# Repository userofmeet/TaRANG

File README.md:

# TaRANG

This repository contains the work I do at EMSys Lab, IIT Bombay, as a Research Assistant during my master's, under the guidance of Prof. Maryam Shojaei Baghini.

It serves as a place to keep the datasheets, research papers, code, and other technical resources related to my work.

## Contents

- Datasheets and technical documentation
- Research papers and references
- Code and implementations
- Experiments and analysis
- Notes and other useful resources

The repository will be updated as I continue working on different tasks and projects in the lab.

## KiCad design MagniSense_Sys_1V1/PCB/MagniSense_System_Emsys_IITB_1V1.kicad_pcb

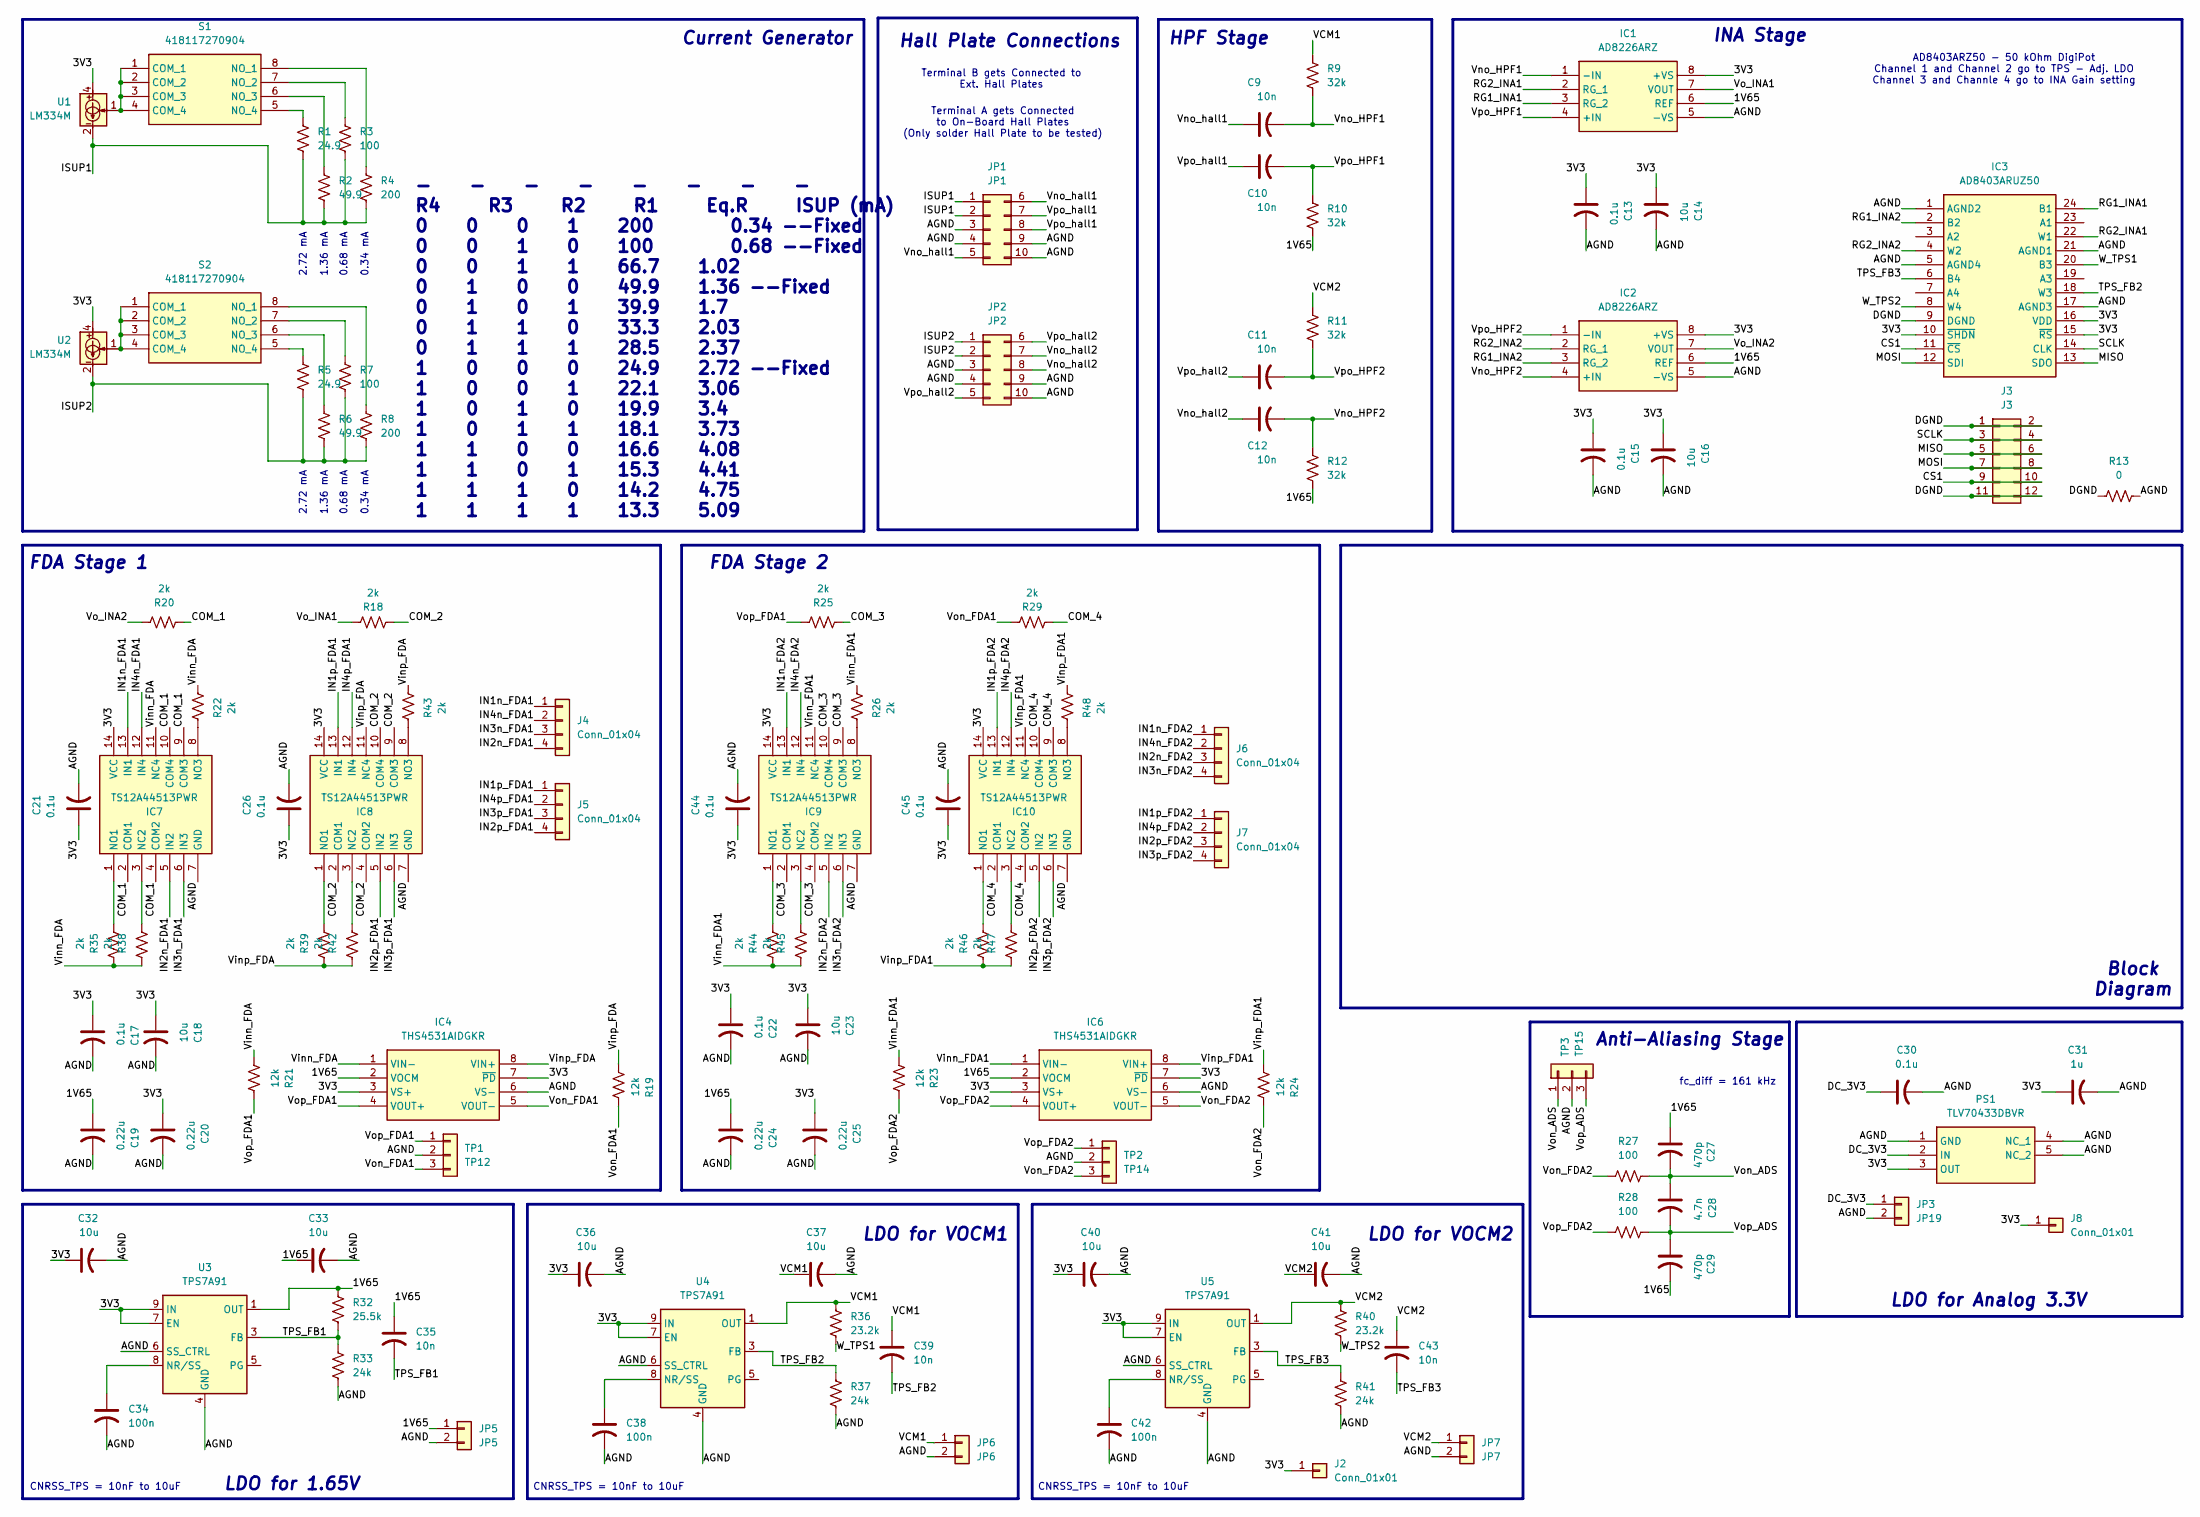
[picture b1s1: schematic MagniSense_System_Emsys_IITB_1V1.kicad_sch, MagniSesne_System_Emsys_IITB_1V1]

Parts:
C9, C10, C11, C12, C35, C39, C43: 10n; C_0603_1608Metric
C13, C15, C17, C21, C22, C26, C30, C44, C45: 0.1u; C_0603_1608Metric
C14, C16, C18, C23, C32, C33, C36, C37, C40, C41: 10u; C_0603_1608Metric
C19, C20, C24, C25: 0.22u; C_0603_1608Metric
C27, C29: 470p; C_0603_1608Metric
C28: 4.7n; C_0603_1608Metric
C31: 1u; C_0603_1608Metric
C34, C38, C42: 100n; C_0603_1608Metric
IC1, IC2: AD8226ARZ; SOIC127P600X175-8N; Manufacturer_Part_Number AD8226ARZ; Mouser Part Number 584-AD8226ARZ
IC3: AD8403ARUZ50; SOP65P640X120-24N; Manufacturer_Part_Number AD8403ARUZ50; Mouser Part Number 584-AD8403ARUZ50
IC4, IC6: THS4531AIDGKR; SOP65P490X110-8N; Manufacturer_Part_Number THS4531AIDGKR; Mouser Part Number 595-THS4531AIDGKR
IC7, IC8, IC9, IC10: TS12A44513PWR; SOP65P640X120-14N; Manufacturer_Part_Number TS12A44513PWR; Mouser Part Number 595-TS12A44513PWR
J2, J8: Conn_01x01; PinHeader_1x01_P2.54mm_Vertical
J3: J3; PinHeader_2x06_P2.54mm_Vertical
J4, J5, J6, J7: Conn_01x04; PinHeader_1x04_P2.54mm_Vertical
JP1: JP1; PinHeader_2x05_P2.54mm_Vertical
JP2: JP2; PinHeader_2x05_P2.54mm_Vertical
JP3: JP19; PinHeader_1x02_P2.54mm_Vertical
JP5: JP5; PinHeader_1x02_P2.54mm_Vertical
JP6: JP6; PinHeader_1x02_P2.54mm_Vertical
JP7: JP7; PinHeader_1x02_P2.54mm_Vertical
PS1: TLV70433DBVR; SOT95P280X145-5N; Manufacturer_Part_Number TLV70433DBVR; Mouser Part Number 595-TLV70433DBVR
R1, R5: 24.9; R_0603_1608Metric
R2, R6: 49.9; R_0603_1608Metric
R3, R7, R27, R28: 100; R_0603_1608Metric
R4, R8: 200; R_0603_1608Metric
R9, R10, R11, R12: 32k; R_0603_1608Metric
R13: 0; R_0603_1608Metric
R18, R20, R22, R25, R26, R29, R35, R38, R39, R42, R43, R44, R45, R46, R47, R48: 2k; R_0603_1608Metric
R19, R21, R23, R24: 12k; R_0603_1608Metric
R32: 25.5k; R_0603_1608Metric
R33, R37, R41: 24k; R_0603_1608Metric
R36, R40: 23.2k; R_0603_1608Metric
S1, S2: 418117270904; Manufacturer_Part_Number 418117270904; Mouser Part Number 710-418117270904
TP1: TP12; PinHeader_1x03_P2.54mm_Vertical
TP2: TP14; PinHeader_1x03_P2.54mm_Vertical
TP3: TP15; PinHeader_1x03_P2.54mm_Vertical
U1, U2: LM334M; SOIC-8_3.9x4.9mm_P1.27mm
U3, U4, U5: TPS7A91; Texas_S-PDSO-N10_EP1.2x2mm

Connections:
/1V65: C19.1, C24.1, C27.1, C29.2, C33.1, C35.1, IC1.6 (REF), IC2.6 (REF), IC4.2 (VOCM), IC6.2 (VOCM), JP5.1, R10.2, R12.2, R32.1, U3.1 (OUT), U3.2 (OUT)
/3V3: C13.1, C14.1, C15.1, C16.1, C17.1, C18.1, C20.1, C21.1, C22.1, C23.1, C25.1, C26.1, C31.1, C32.1, C36.1, C40.1, C44.1, C45.1, IC1.8 (+VS), IC2.8 (+VS), IC3.10 (~SHDN), IC3.15 (~RS), IC3.16 (VDD), IC4.3 (VS+), IC4.7 (~PD), IC6.3 (VS+), IC6.7 (~PD), IC7.14 (VCC), IC8.14 (VCC), IC9.14 (VCC), IC10.14 (VCC), J2.1 (Pin_1_1), J8.1 (Pin_1_1), PS1.3 (OUT), U1.4, U2.4, U3.7 (EN), U3.9 (IN), U3.10 (IN), U4.7 (EN), U4.9 (IN), U4.10 (IN), U5.7 (EN), U5.9 (IN), U5.10 (IN)
/AGND: C13.2, C14.2, C15.2, C16.2, C17.2, C18.2, C19.2, C20.2, C21.2, C22.2, C23.2, C24.2, C25.2, C26.2, C30.2, C31.2, C32.2, C33.2, C34.2, C36.2, C37.2, C38.2, C40.2, C41.2, C42.2, C44.2, C45.2, IC1.5 (-VS), IC2.5 (-VS), IC3.1 (AGND2), IC3.5 (AGND4), IC3.17 (AGND3), IC3.21 (AGND1), IC4.6 (VS-), IC6.6 (VS-), IC7.7 (GND), IC8.7 (GND), IC9.7 (GND), IC10.7 (GND), JP1.3, JP1.4, JP1.9, JP1.10, JP2.3, JP2.4, JP2.9, JP2.10, JP3.2, JP5.2, JP6.2, JP7.2, PS1.1 (GND), PS1.4 (NC_1), PS1.5 (NC_2), R13.2, R33.2, R37.2, R41.2, TP1.2, TP2.2, TP3.2, U3.4 (GND), U3.6 (SS_CTRL), U3.11 (GND), U4.4 (GND), U4.6 (SS_CTRL), U4.11 (GND), U5.4 (GND), U5.6 (SS_CTRL), U5.11 (GND)
/COM_1: IC7.2 (COM1), IC7.4 (COM2), IC7.9 (COM3), IC7.10 (COM4), R20.2
/COM_2: IC8.2 (COM1), IC8.4 (COM2), IC8.9 (COM3), IC8.10 (COM4), R18.1
/COM_3: IC9.2 (COM1), IC9.4 (COM2), IC9.9 (COM3), IC9.10 (COM4), R25.2
/COM_4: IC10.2 (COM1), IC10.4 (COM2), IC10.9 (COM3), IC10.10 (COM4), R29.1
/CS1: IC3.11 (~CS), J3.9, J3.10
/DC_3V3: C30.1, JP3.1, PS1.2 (IN)
/DGND: IC3.9 (DGND), J3.1, J3.2, J3.11, J3.12, R13.1
/IN1n_FDA1: IC7.13 (IN1), J4.1
/IN1n_FDA2: IC9.13 (IN1), J6.1
/IN1p_FDA1: IC8.13 (IN1), J5.1
/IN1p_FDA2: IC10.13 (IN1), J7.1
/IN2n_FDA1: IC7.5 (IN2), J4.4
/IN2n_FDA2: IC9.5 (IN2), J6.3
/IN2p_FDA1: IC8.5 (IN2), J5.4
/IN2p_FDA2: IC10.5 (IN2), J7.3
/IN3n_FDA1: IC7.6 (IN3), J4.3
/IN3n_FDA2: IC9.6 (IN3), J6.4
/IN3p_FDA1: IC8.6 (IN3), J5.3
/IN3p_FDA2: IC10.6 (IN3), J7.4
/IN4n_FDA1: IC7.12 (IN4), J4.2
/IN4n_FDA2: IC9.12 (IN4), J6.2
/IN4p_FDA1: IC8.12 (IN4), J5.2
/IN4p_FDA2: IC10.12 (IN4), J7.2
/ISUP1: JP1.1, JP1.2, R1.1, R2.1, R3.1, R4.2, U1.2, U1.3, U1.6, U1.7
/ISUP2: JP2.1, JP2.2, R5.1, R6.1, R7.1, R8.2, U2.2, U2.3, U2.6, U2.7
/MISO: IC3.13 (SDO), J3.5, J3.6
/MOSI: IC3.12 (SDI), J3.7, J3.8
/RG1_INA1: IC1.3 (RG_2), IC3.24 (B1)
/RG1_INA2: IC2.3 (RG_2), IC3.2 (B2)
/RG2_INA1: IC1.2 (RG_1), IC3.22 (W1)
/RG2_INA2: IC2.2 (RG_1), IC3.4 (W2)
/SCLK: IC3.14 (CLK), J3.3, J3.4
/TPS_FB1: C35.2, R32.2, R33.1, U3.3 (FB)
/TPS_FB2: C39.2, IC3.18 (W3), R37.1, U4.3 (FB)
/TPS_FB3: C43.2, IC3.6 (B4), R41.1, U5.3 (FB)
/VCM1: C37.1, C39.1, JP6.1, R9.1, R36.1, U4.1 (OUT), U4.2 (OUT)
/VCM2: C41.1, C43.1, JP7.1, R11.1, R40.1, U5.1 (OUT), U5.2 (OUT)
/Vinn_FDA: IC4.1 (VIN-), IC7.11 (NC4), R21.1, R22.1, R35.1, R38.1
/Vinn_FDA1: IC6.1 (VIN-), IC9.11 (NC4), R23.1, R26.1, R44.1, R45.1
/Vinp_FDA: IC4.8 (VIN+), IC8.11 (NC4), R19.1, R39.1, R42.1, R43.1
/Vinp_FDA1: IC6.8 (VIN+), IC10.11 (NC4), R24.1, R46.1, R47.1, R48.1
/Vno_HPF1: C9.2, IC1.1 (-IN), R9.2
/Vno_HPF2: C12.2, IC2.4 (+IN), R12.1
/Vno_hall1: C9.1, JP1.5, JP1.6
/Vno_hall2: C12.1, JP2.7, JP2.8
/Vo_INA1: IC1.7 (VOUT), R18.2
/Vo_INA2: IC2.7 (VOUT), R20.1
/Von_ADS: C27.2, C28.1, R27.2, TP3.1
/Von_FDA1: IC4.5 (VOUT-), R19.2, R29.2, TP1.3
/Von_FDA2: IC6.5 (VOUT-), R24.2, R27.1, TP2.3
/Vop_ADS: C28.2, C29.1, R28.2, TP3.3
/Vop_FDA1: IC4.4 (VOUT+), R21.2, R25.1, TP1.1
/Vop_FDA2: IC6.4 (VOUT+), R23.2, R28.1, TP2.1
/Vpo_HPF1: C10.2, IC1.4 (+IN), R10.1
/Vpo_HPF2: C11.2, IC2.1 (-IN), R11.2
/Vpo_hall1: C10.1, JP1.7, JP1.8
/Vpo_hall2: C11.1, JP2.5, JP2.6
/W_TPS1: IC3.20 (B3), R36.2
/W_TPS2: IC3.8 (W4), R40.2
unnamed: IC7.3 (NC2), R38.2
unnamed: IC7.1 (NO1), R35.2
unnamed: IC7.8 (NO3), R22.2
unnamed: IC8.3 (NC2), R42.2
unnamed: IC8.1 (NO1), R39.2
unnamed: IC8.8 (NO3), R43.2
unnamed: IC9.3 (NC2), R45.2
unnamed: IC9.1 (NO1), R44.2
unnamed: IC9.8 (NO3), R26.2
unnamed: IC10.3 (NC2), R47.2
unnamed: IC10.1 (NO1), R46.2
unnamed: IC10.8 (NO3), R48.2
unnamed: S1.1 (COM_1), S1.2 (COM_2), S1.3 (COM_3), S1.4 (COM_4), U1.1
unnamed: R4.1, S1.8 (NO_1)
unnamed: R3.2, S1.7 (NO_2)
unnamed: R2.2, S1.6 (NO_3)
unnamed: R1.2, S1.5 (NO_4)
unnamed: S2.1 (COM_1), S2.2 (COM_2), S2.3 (COM_3), S2.4 (COM_4), U2.1
unnamed: R8.1, S2.8 (NO_1)
unnamed: R7.2, S2.7 (NO_2)
unnamed: R6.2, S2.6 (NO_3)
unnamed: R5.2, S2.5 (NO_4)
unnamed: C34.1, U3.8 (NR/SS)
unnamed: C38.1, U4.8 (NR/SS)
unnamed: C42.1, U5.8 (NR/SS)

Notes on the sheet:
INA Stage
fc_diff = 161 kHz
2.72 mA
CNRSS_TPS = 10nF to 10uF
1.36 mA
0.34 mA
AD8403ARZ50 - 50 kOhm DigiPot Channel 1 and Channel 2 go to TPS - Adj. LDO Channel 3 and Channle 4 go to INA Gain setting
0.68 mA
Anti-Aliasing Stage
Current Generator
HPF Stage
LDO for VOCM1
Terminal B gets Connected to Ext. Hall Plates
Block Diagram
LDO for Analog 3.3V
LDO for 1.65V
FDA Stage 1
Hall Plate Connections
FDA Stage 2
Terminal A gets Connected to On-Board Hall Plates (Only solder Hall Plate to be tested)
LDO for VOCM2
- - - - - - - - R4 R3 R2 R1 Eq.R ISUP (mA) 0 0 0 1 200 0.34 --Fixed 0 0 1 0 100 0.68 --Fixed 0 0 1 1 66.7 1.02 0 1 0 0 49.9 1.36 --Fixed 0 1 0 1 39.9 1.7 0 1 1 0 33.3 2.03 0 1 1 1 28.5 2.37 1 0 0 0 24.9 2.72 --Fixed 1 0 0 1 22.1 3.06 1 0 1 0 19.9 3.4 1 0 1 1 18.1 3.73 1 1 0 0 16.6 4.08 1 1 0 1 15.3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

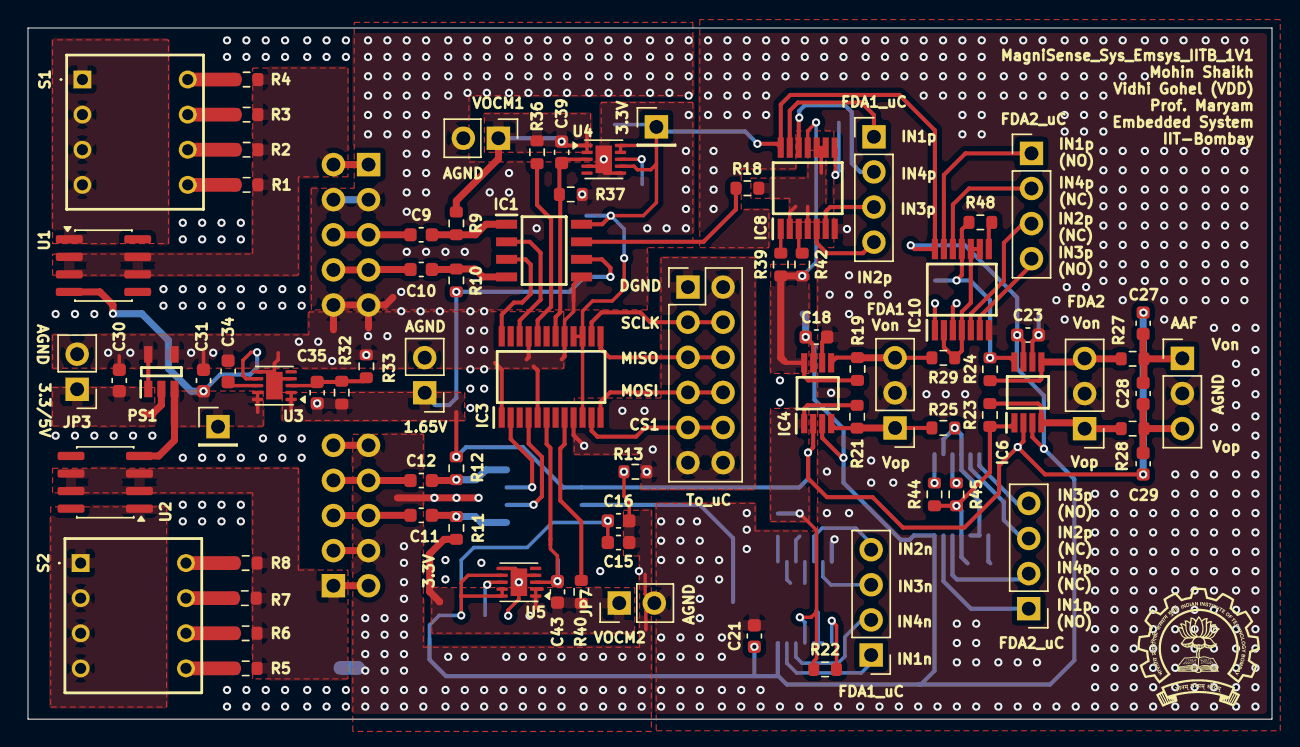
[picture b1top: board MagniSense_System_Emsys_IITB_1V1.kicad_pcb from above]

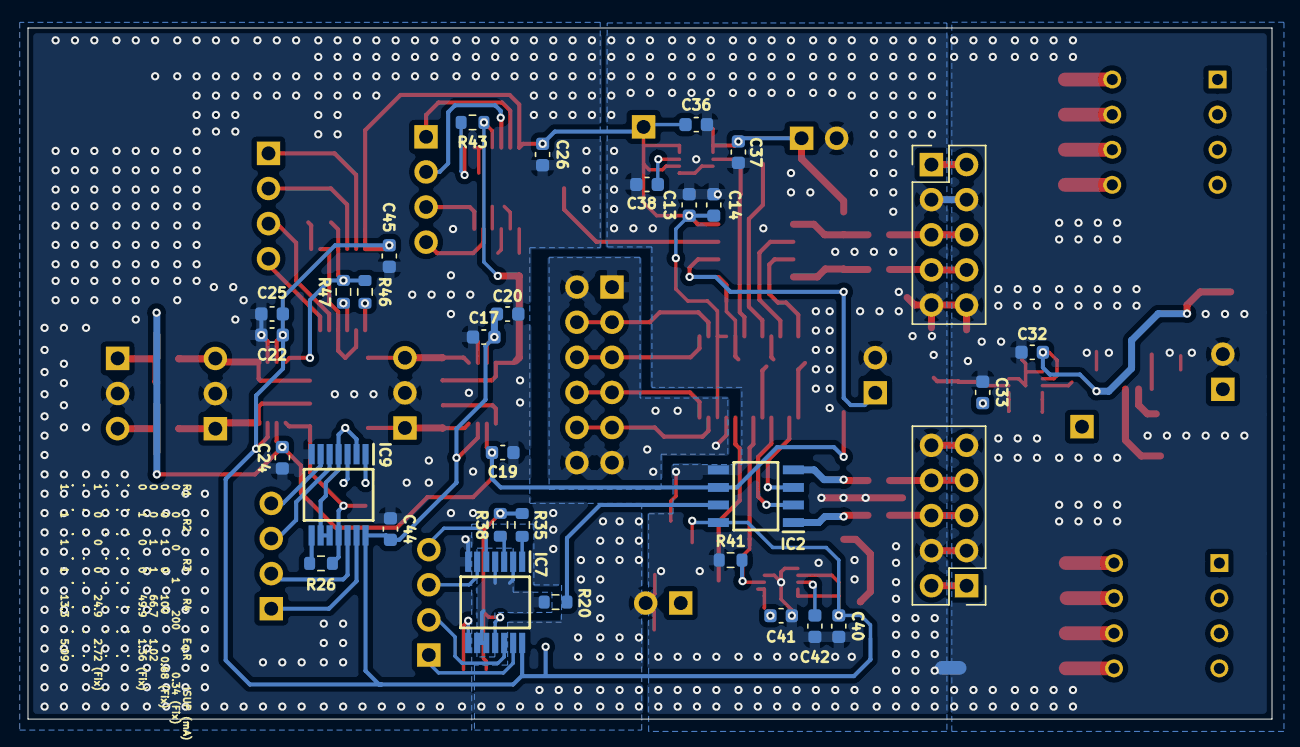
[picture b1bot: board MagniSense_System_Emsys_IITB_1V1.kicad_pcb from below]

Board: 2 copper layers, 90.0 x 50.0 mm, 111 parts (32 on the bottom side), 87 nets.
